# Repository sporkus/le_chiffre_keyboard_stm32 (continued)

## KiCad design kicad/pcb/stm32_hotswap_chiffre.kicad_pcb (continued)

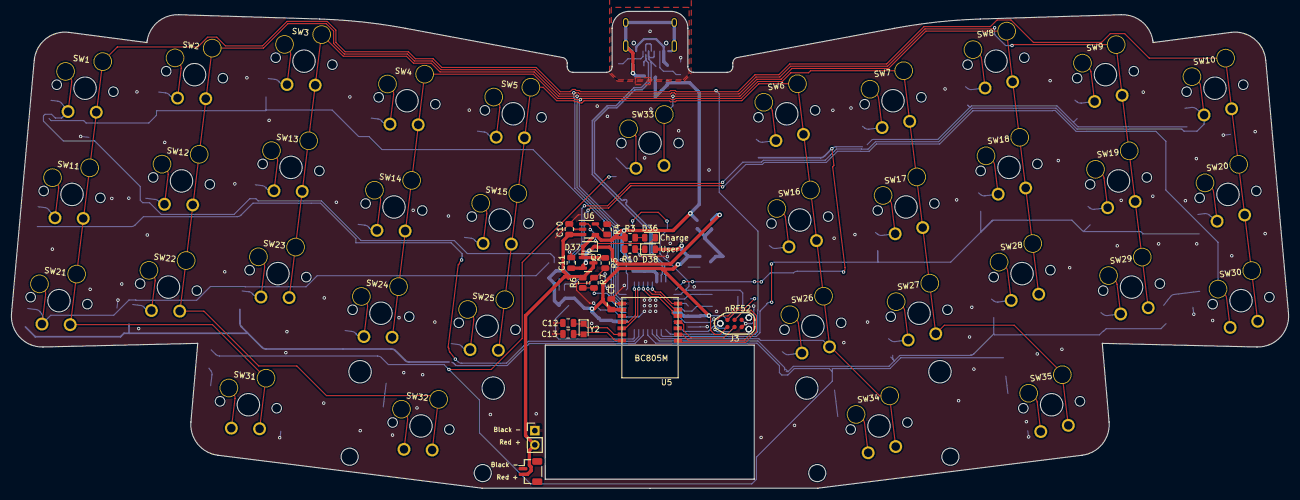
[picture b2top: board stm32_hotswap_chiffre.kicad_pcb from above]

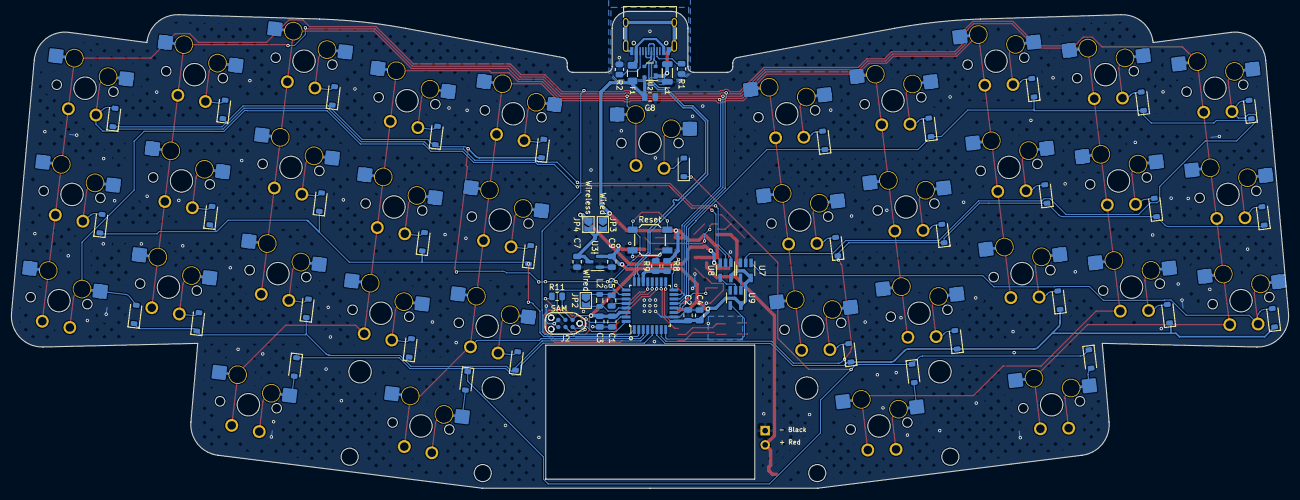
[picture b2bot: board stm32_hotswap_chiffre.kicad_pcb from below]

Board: 2 copper layers, 227.3 x 84.8 mm, 119 parts (63 on the bottom side), 84 nets.

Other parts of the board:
C7, C9: 1uF; C_0805_2012Metric

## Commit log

2023-06-25 routed pcb
2023-06-25 docs
2023-06-25 more bom work
2023-06-25 testing kibot
2023-06-25 gh workflow
2023-06-25 specify kibot target
2023-06-26 workflow tweak?
2023-06-26 kibot workflow tweak?
2023-06-26 non-wildcard kibot workflow
2023-06-26 encoder debounce caps + verified CPL
2023-06-26 silkscreen clean up
2023-06-26 update 3d models
2023-06-26 version freeze
2023-06-27 esd and usb update/
2023-06-28 rerouted for better grounding
2023-06-29 cleaning up pcb
2023-07-09 v0.2
2023-07-09 adding firmware
2023-07-13 v0.2 release
2023-07-13 doc fix
2023-07-13 adding front LED bypass jumper
2023-07-14 exporting edgecut dxf
2023-07-18 adding panelized plate files
2023-07-20 adding panelized plate
2023-07-20 change center switch footprint
2023-07-20 add kibot documentation
2023-07-20 [kibot]
2023-07-20 finishing up details
2023-07-26 v0.2.2
2023-08-02 add keycap models
2023-08-02 adding a case
2023-08-03 add plate files
2023-09-08 add alps+mx plate
2023-09-08 alps plate should be 1.2mm
2023-09-11 smaller mousebite on plate
2023-09-15 add QR code
2023-09-18 adding plain top stl
2023-09-28 adding top case with keycap cutout
2023-10-29 Chiffre RGB indicator fixes
    * Reduced default brightness
    * Uses a new config parameter `RGB_INDICATOR_BRIGHTNESS` to separate the
    control of front leds from the back leds
    * Fix the RGB indicator enable/disable code
2023-12-11 Initial SAM/nRF52 version.
2023-12-11 Initial kibot tweaks for gerber artifacts.
2023-12-11 Try two on MX plates.
2023-12-11 Newer upload action.
2023-12-11 PCB kibot bits.
2024-02-26 fix pin order
2024-03-02 add 36 key kicad
2024-03-06 fix schematic on right thumb keys
2024-03-06 minor touch ups
2026-05-02 update firmware
2026-05-02 Update firmware section in README
    Updated firmware section to include Vial source and link to firmware directory.
2026-05-02 Add vial firmware
2026-05-02 add notes
2026-05-02 update gh action
2026-05-02 clean up
